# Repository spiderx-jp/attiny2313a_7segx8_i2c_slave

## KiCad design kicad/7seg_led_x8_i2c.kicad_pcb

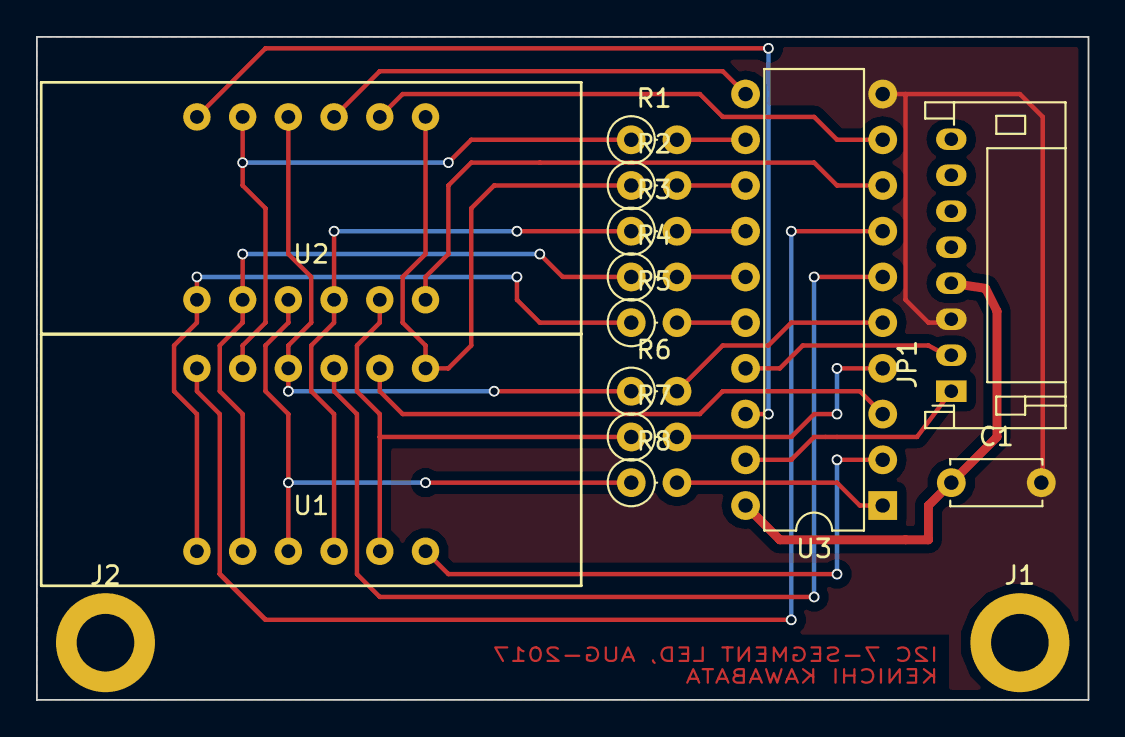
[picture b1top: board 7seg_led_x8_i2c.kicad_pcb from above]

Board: 2 copper layers, 58.4 x 36.8 mm, 15 parts (0 on the bottom side), 28 nets.

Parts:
C1: 0.1u; C_Disc_D5.0mm_W2.5mm_P5.00mm
J1: hole1; MountingHole_3.2mm_M3_ISO14580_Pad
J2: hole2; MountingHole_3.2mm_M3_ISO14580_Pad
JP1: JP_8P; JST_PH_S8B-PH-K_08x2.00mm_Angled
R1, R2, R3, R4, R5, R6, R7, R8: 270; R_Axial_DIN0207_L6.3mm_D2.5mm_P2.54mm_Vertical
U1, U2: NFD-3641
U3: ATTINY2313-20PU; DIP-20_W7.62mm

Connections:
+3V3: C1.1, JP1.4, U3.20
/A: R1.2, U3.12
/B: R2.2, U3.13
/C: R3.2, U3.14
/D: R4.2, U3.15
/DP: R8.2, U3.1
/E: R5.2, U3.16
/F: R6.2, U3.5
/G: R7.2, U3.4
/LED1: U2.12, U3.18
/LED2: U2.9, U3.11
/LED3: U2.8, U3.9
/LED4: U2.6, U3.8
/LED5: U1.12, U3.7
/LED6: U1.9, U3.6
/LED7: U1.8, U3.3
/LED8: U1.6, U3.2
GND: C1.2, JP1.3, U3.10
unnamed: JP1.1, U3.19
unnamed: JP1.2, U3.17
unnamed: R1.1, U1.11, U2.11
unnamed: R2.1, U1.7, U2.7
unnamed: R3.1, U1.4, U2.4
unnamed: R4.1, U1.2, U2.2
unnamed: R5.1, U1.1, U2.1
unnamed: R6.1, U1.10, U2.10
unnamed: R7.1, U1.5, U2.5
unnamed: R8.1, U1.3, U2.3

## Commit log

2017-09-02 Initial
2017-09-10 Added Test I2C Master Program
    This is a program cord to test ATTINY2313A 7segment x8 i2c slave module.
    USI I2C Master is TI MSP430F2013.
